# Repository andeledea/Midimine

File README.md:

# Midimine
Midi controller project pcb and code

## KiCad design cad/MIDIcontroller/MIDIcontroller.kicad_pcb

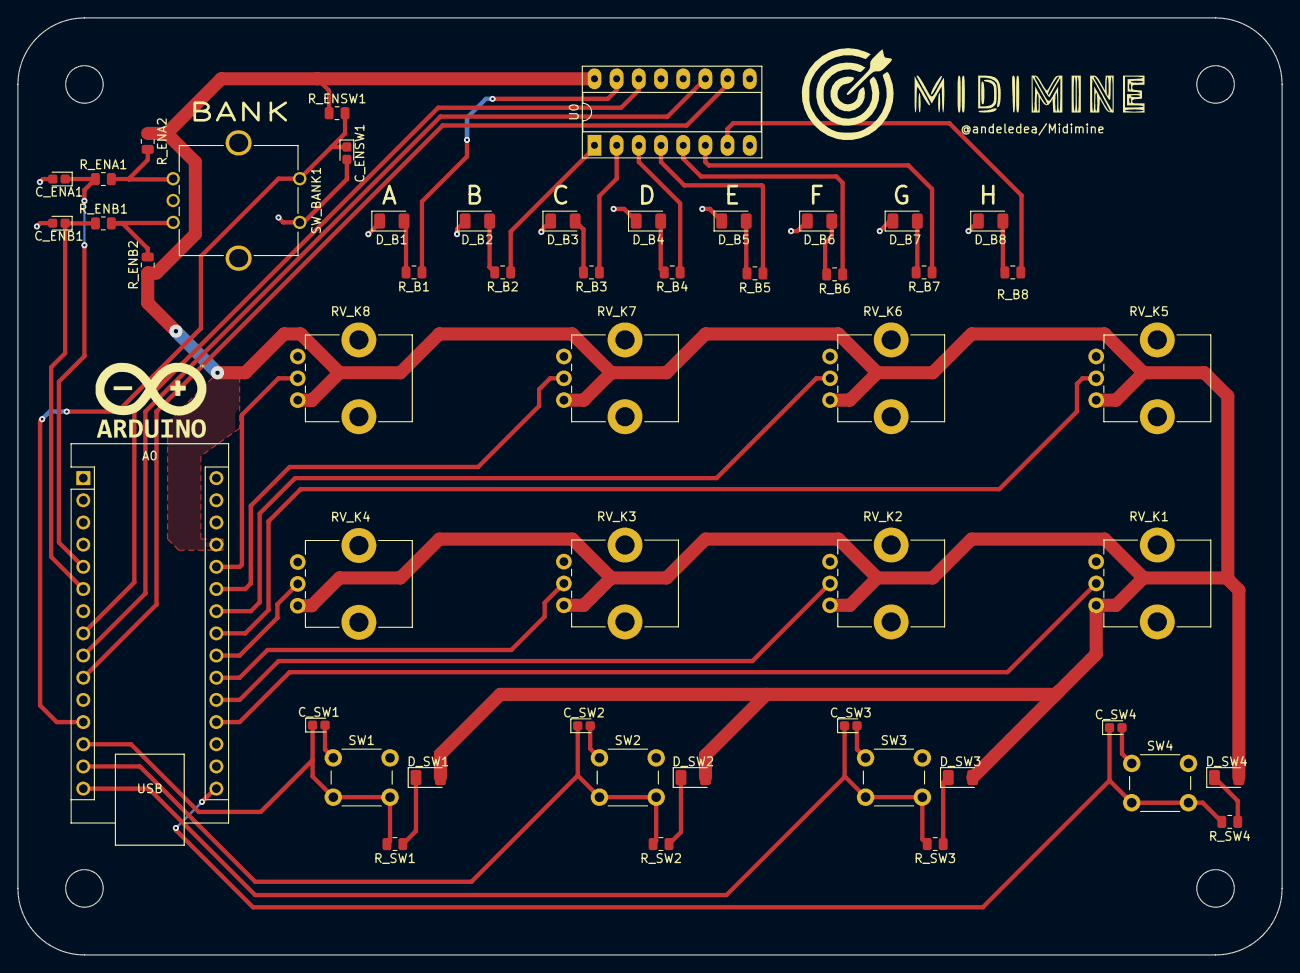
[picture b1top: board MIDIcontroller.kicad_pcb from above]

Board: 2 copper layers, 144.8 x 107.3 mm, 55 parts (0 on the bottom side), 42 nets.

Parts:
A0: Arduino_Nano_v2.x; Arduino_Nano
C_ENA1: 10n; CP_EIA-1608-08_AVX-J
C_ENB1: 10n; CP_EIA-1608-08_AVX-J
C_ENSW1: 220n; CP_EIA-1608-08_AVX-J
C_SW1, C_SW2, C_SW3, C_SW4: 220n; CP_EIA-1608-08_AVX-J
D_B1, D_B2, D_B3, D_B4, D_B5, D_B6, D_B7, D_B8: LED; LED_1206_3216Metric
D_SW1, D_SW2, D_SW3, D_SW4: LED; LED_1206_3216Metric
H1, H2, H3, H4: MountingHole; MountingHole_4.3mm_M4
RV_K1, RV_K2, RV_K3, RV_K4, RV_K5, RV_K6, RV_K7, RV_K8: 500k; Potentiometer_Bourns_PTV09A-1_Single_Vertical
R_B1, R_B2, R_B3, R_B4, R_B5, R_B6, R_B7, R_B8: 330; R_0805_2012Metric
R_ENA1, R_ENA2: 10k; R_0805_2012Metric
R_ENB1, R_ENB2: 10k; R_0805_2012Metric
R_ENSW1: 10k; R_0805_2012Metric
R_SW1, R_SW2, R_SW3, R_SW4: 330; R_0805_2012Metric
SW1, SW2, SW3, SW4: SW_Push_Dual; SW_PUSH_6mm_H5mm
SW_BANK1: RotaryEncoder; RotaryEncoder_Bourns_Vertical_PEC12R-3xxxF-Sxxxx
U0: 74HC595; DIP-16_W7.62mm_Socket_LongPads

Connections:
5V: A0.27 (+5V), D_SW1.2 (A), D_SW2.2 (A), D_SW3.2 (A), D_SW4.2 (A), RV_K1.1, RV_K2.1, RV_K3.1, RV_K4.1, RV_K5.1, RV_K6.1, RV_K7.1, RV_K8.1, R_ENA2.1, R_ENB2.1, R_ENSW1.1, U0.16 (VCC)
DS: A0.8 (D5), U0.14 (SER)
EN_S1: A0.12 (D9), C_ENSW1.1, R_ENSW1.2, SW_BANK1.S1
EN_S2: A0.4 (GND), A0.29 (GND), C_ENA1.2, C_ENB1.2, C_ENSW1.2, C_SW1.2, C_SW2.2, C_SW3.2, C_SW4.2, D_B1.1 (K), D_B2.1 (K), D_B3.1 (K), D_B4.1 (K), D_B5.1 (K), D_B6.1 (K), D_B7.1 (K), D_B8.1 (K), RV_K1.3, RV_K2.3, RV_K3.3, RV_K4.3, RV_K5.3, RV_K6.3, RV_K7.3, RV_K8.3, SW1.1, SW2.1, SW3.1, SW4.1, SW_BANK1.C, SW_BANK1.S2, U0.8 (GND)
Encoder_A: A0.5 (D2), C_ENA1.1, R_ENA1.1
Encoder_B: A0.6 (D3), C_ENB1.1, R_ENB1.1
Knob1: A0.19 (A0), RV_K1.2
Knob2: A0.20 (A1), RV_K2.2
Knob3: A0.21 (A2), RV_K3.2
Knob4: A0.22 (A3), RV_K4.2
Knob5: A0.23 (A4), RV_K5.2
Knob6: A0.24 (A5), RV_K6.2
Knob7: A0.25 (A6), RV_K7.2
Knob8: A0.26 (A7), RV_K8.2
unnamed: D_B1.2 (A), R_B1.2
unnamed: D_B2.2 (A), R_B2.2
unnamed: D_B3.2 (A), R_B3.2
unnamed: D_B4.2 (A), R_B4.2
unnamed: D_B5.2 (A), R_B5.2
unnamed: D_B6.2 (A), R_B6.2
unnamed: D_B7.2 (A), R_B7.2
unnamed: D_B8.2 (A), R_B8.2
unnamed: D_SW1.1 (K), R_SW1.1
unnamed: D_SW2.1 (K), R_SW2.1
unnamed: D_SW3.1 (K), R_SW3.1
unnamed: D_SW4.1 (K), R_SW4.1
unnamed: R_B1.1, U0.15 (QA)
unnamed: R_B2.1, U0.1 (QB)
unnamed: R_B3.1, U0.2 (QC)
unnamed: R_B4.1, U0.3 (QD)
unnamed: R_B5.1, U0.4 (QE)
unnamed: R_B6.1, U0.5 (QF)
unnamed: R_B7.1, U0.6 (QG)
unnamed: R_B8.1, U0.7 (QH)
unnamed: R_ENA1.2, R_ENA2.2, SW_BANK1.A
unnamed: R_ENB1.2, R_ENB2.2, SW_BANK1.B
SHCP: A0.9 (D6), U0.11 (SRCLK)
STCP: A0.10 (D7), U0.10 (~SRCLR)
SW1: A0.13 (D10), C_SW1.1, R_SW1.2, SW1.2
SW2: A0.14 (D11), C_SW2.1, R_SW2.2, SW2.2
SW3: A0.15 (D12), C_SW3.1, R_SW3.2, SW3.2
SW4: A0.16 (D13), C_SW4.1, R_SW4.2, SW4.2

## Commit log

2023-01-25 Started routing
2023-01-25 added serigrafie
2023-01-26 Added button on encoder
